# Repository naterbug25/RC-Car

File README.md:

# RC-Car
RC Car using NRF24L01 Radios with multi channel selection. 

Read the manual under "Documents"

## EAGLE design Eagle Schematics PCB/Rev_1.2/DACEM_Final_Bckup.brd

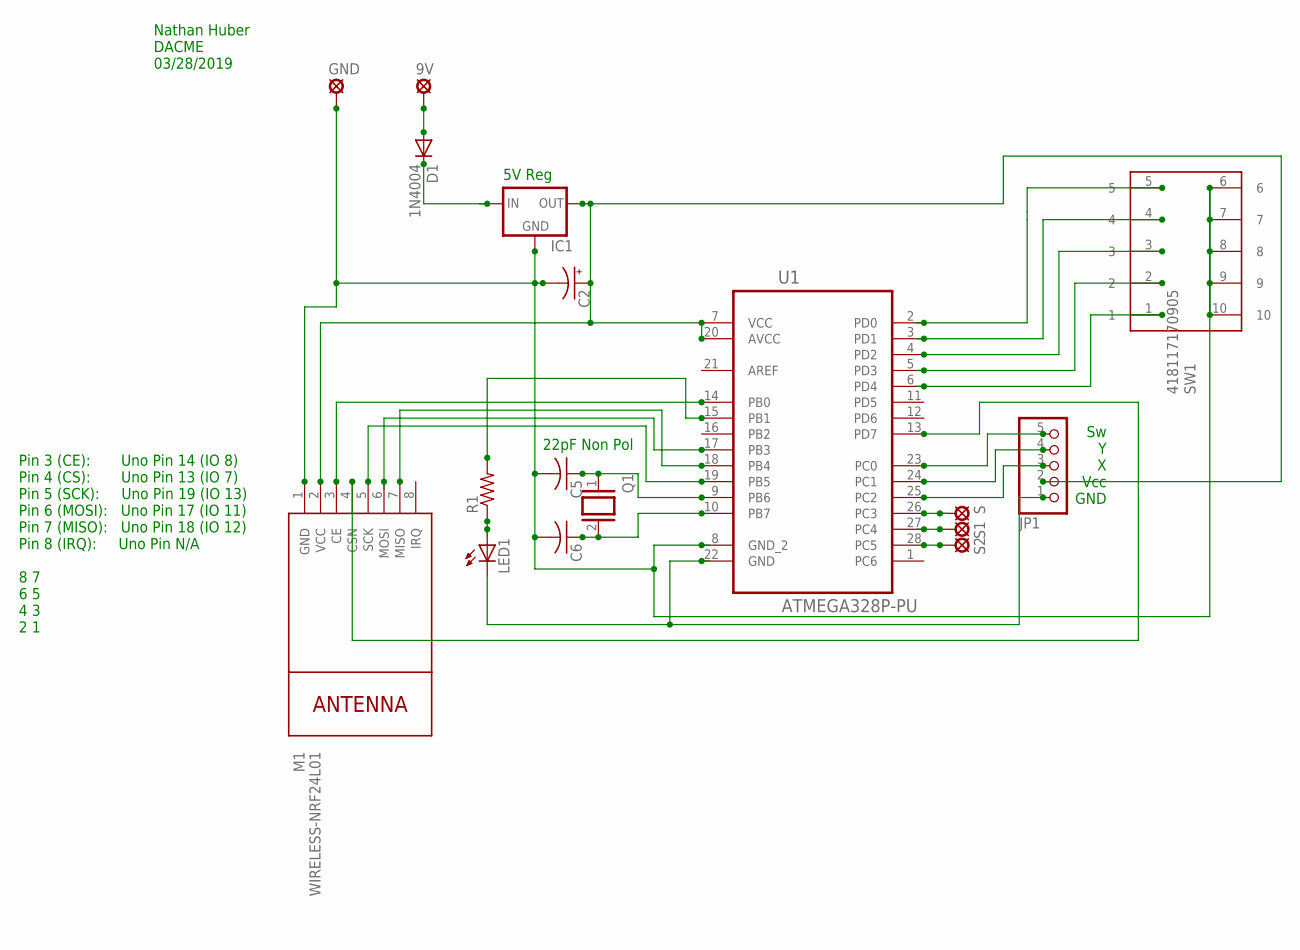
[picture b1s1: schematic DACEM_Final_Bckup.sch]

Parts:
9V: LSP10
C2: CPOL-USE1.8-4; E1,8-4
C5, C6: C-US025-025X050; C025-025X050
D1: 1N4004; DO41-10
GND: LSP10
IC1: 78XXS
JP1: PINHD-1X5; 1X05
LED1: LED3MM
M1: WIRELESS-NRF24L01
Q1: XTAL; Q
R1: R-US_0207/15; 0207/15
S, S1, S2: LSP10
SW1: 418117170905
U1: ATMEGA328P-PU; DIP254P762X457-28

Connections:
unnamed: C2.-, C5.2, C6.2, GND.MP, IC1.GND, M1.1 (GND), SW1.6, SW1.7, SW1.8, SW1.9, SW1.10, U1.8 (GND_2)
unnamed: M1.7 (MISO), U1.18 (PB4)
unnamed: JP1.5, U1.23 (PC0)
unnamed: C2.+, IC1.OUT, JP1.2, M1.2 (VCC), U1.7 (VCC), U1.20 (AVCC)
unnamed: SW1.5, U1.2 (PD0)
unnamed: JP1.1, LED1.K (C), U1.22 (GND)
unnamed: JP1.4, U1.24 (PC1)
unnamed: JP1.3, U1.25 (PC2)
unnamed: C6.1, Q1.2, U1.10 (PB7)
unnamed: SW1.4, U1.3 (PD1)
unnamed: SW1.3, U1.4 (PD2)
unnamed: C5.1, Q1.1, U1.9 (PB6)
unnamed: SW1.2, U1.5 (PD3)
unnamed: M1.3 (CE), U1.14 (PB0)
unnamed: M1.4 (CSN), U1.13 (PD7)
unnamed: M1.5 (SCK), U1.19 (PB5)
unnamed: M1.6 (MOSI), U1.17 (PB3)
unnamed: SW1.1, U1.6 (PD4)
unnamed: R1.2, U1.15 (PB1)
unnamed: LED1.A, R1.1
unnamed: D1.C, IC1.IN
unnamed: 9V.MP, D1.A
unnamed: S.MP, U1.26 (PC3)
unnamed: S1.MP, U1.27 (PC4)
unnamed: S2.MP, U1.28 (PC5)

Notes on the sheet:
5V Reg
Sw Y X Vcc GND
22pF Non Pol
Pin 3 (CE): Uno Pin 14 (IO 8) Pin 4 (CS): Uno Pin 13 (IO 7) Pin 5 (SCK): Uno Pin 19 (IO 13) Pin 6 (MOSI): Uno Pin 17 (IO 11) Pin 7 (MISO): Uno Pin 18 (IO 12) Pin 8 (IRQ): Uno Pin N/A 8 7 6 5 4 3 2 1
Nathan Huber DACME 03/28/2019

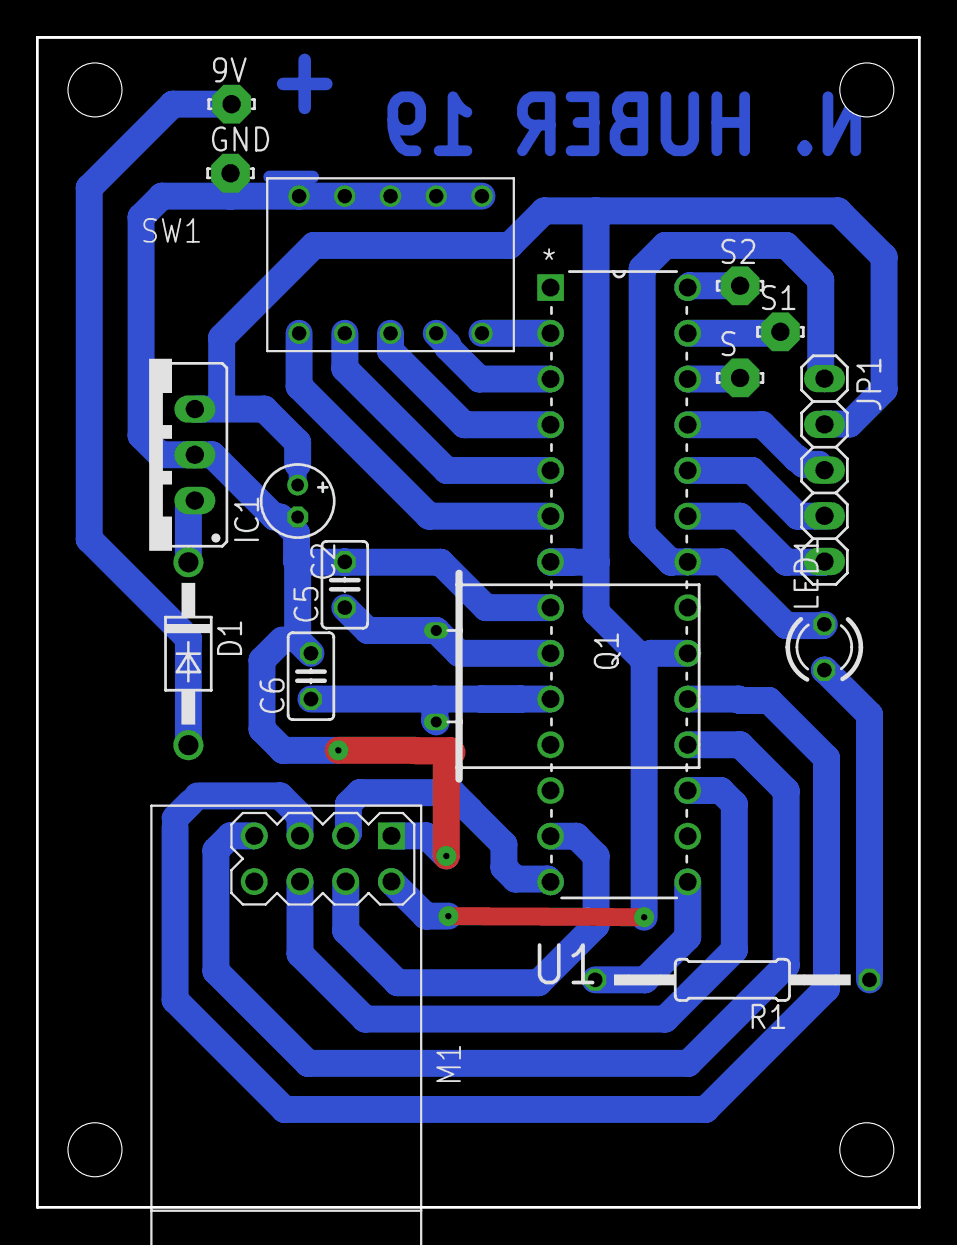
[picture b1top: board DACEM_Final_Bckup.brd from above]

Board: 2 copper layers, 49.0 x 65.0 mm, 17 parts (0 on the bottom side), 25 nets.

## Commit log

2019-04-29 Create delete

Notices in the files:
parts and their libraries:
diy-modules: Released under the Creative Commons Attribution 4.0 International License: http://creativecommons.org/licenses/by/4.0
Dip_Switch: Copyright: Würth Elektronik
